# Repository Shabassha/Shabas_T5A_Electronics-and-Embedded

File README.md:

# 40V DC Motor H-Bridge Controller

## Overview
This repository contains the design files, simulations, and documentation for a 40V DC motor H-Bridge circuit capable of bidirectional control. The design was developed using a multi-stage validation approach: verifying the high-voltage logic and bootstrap physics in **Proteus**, followed by physical footprint mapping and PCB routing in **KiCad**.

## Key Features
* **High-Voltage Operation:** Designed to safely switch a 40V motor supply rail.
* **Hardware Shoot-Through Protection:** Utilizes dual IR2104 half-bridge gate drivers with built-in dead-time insertion, preventing cross-conduction.
* **Bootstrap Circuitry:** Integrated 10µF capacitors and fast-recovery diodes to safely drive the high-side N-Channel MOSFETs.
* **Optimized Power Routing:** High-current paths (40V IN, Motor Outputs) are routed with 1.5mm traces, while logic signals use standard 0.25mm traces.
* **Thermal Management:** Features a continuous bottom-layer copper ground pour to dissipate heat and shield logic inputs from high-voltage switching noise.

## Core Components
* **Gate Drivers:** 2x IR2104 (DIP-8)
* **Power MOSFETs:** 4x IRF540N (N-Channel, TO-220)
* **Terminals:** 5.08mm screw terminal blocks (Power & Motor), 2.54mm pin headers (Logic)
* **Passives:** 20Ω series gate resistors, 10µF radial electrolytic capacitors

## Repository Structure
* `/KiCad/` - Contains the schematic (`.kicad_sch`), PCB layout (`.kicad_pcb`), and 3D renders.
* `/Simulation/` - Contains the Proteus project files used to validate the gate driver logic.
* `/Docs/` - Contains the Bill of Materials (BOM) and the comprehensive Phase 2 Design Report (PDF).

## Getting Started
To view or modify the physical board layout:
1. Clone this repository.
2. Open the project file in [KiCad](https://www.kicad.org/).
3. To view the physical board, open the PCB Editor and press `Alt+3` to launch the 3D Viewer.

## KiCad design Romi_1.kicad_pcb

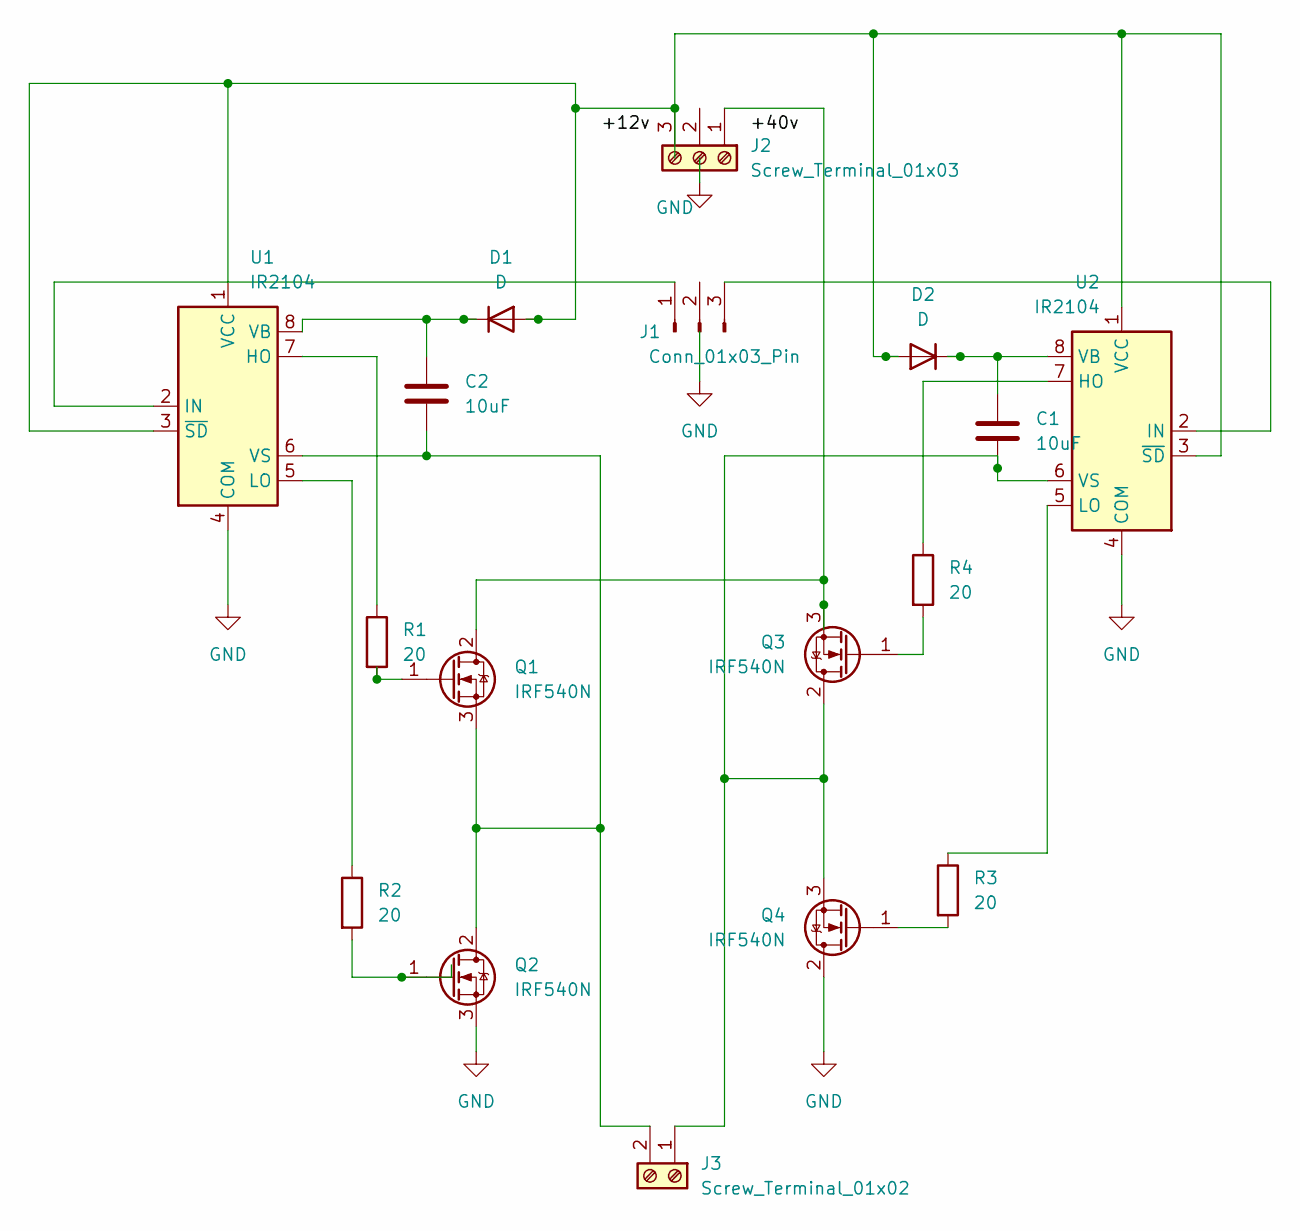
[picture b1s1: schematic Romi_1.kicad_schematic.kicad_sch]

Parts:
C1, C2: 10uF; CP_Radial_D5.0mm_P2.50mm
D1, D2: D; D_DO-41_SOD81_P10.16mm_Horizontal
J1: Conn_01x03_Pin; PinHeader_1x03_P2.54mm_Vertical
J2: Screw_Terminal_01x03; TerminalBlock_Phoenix_MKDS-1,5-3-5.08_1x03_P5.08mm_Horizont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
J3: Screw_Terminal_01x02; TerminalBlock_Phoenix_MKDS-1,5-2-5.08_1x02_P5.08mm_Horizont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
Q1, Q2, Q3, Q4: IRF540N; TO-220-3_Vertical
R1, R2, R3, R4: 20; R_Axial_DIN0207_L6.3mm_D2.5mm_P10.16mm_Horizontal
U1, U2: IR2104; DIP-8_W7.62mm

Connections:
GND: Q2.3 (S), Q4.2 (D), U1.4 (COM), U2.4 (COM)
unnamed: D1.2 (A), D2.2 (A), J2.3, U1.1 (VCC), U1.3 (~SD), U2.1 (VCC), U2.3 (~SD)
unnamed: C2.1, D1.1 (K), U1.8 (VB)
unnamed: C1.1, D2.1 (K), U2.8 (VB)
unnamed: J1.1, U1.2 (IN)
unnamed: J1.3, U2.2 (IN)
unnamed: J2.1, Q1.2 (D), Q3.3 (S)
unnamed: C1.2, J3.1, Q3.2 (D), Q4.3 (S), U2.6 (VS)
unnamed: C2.2, J3.2, Q1.3 (S), Q2.2 (D), U1.6 (VS)
unnamed: Q1.1 (G), R1.2
unnamed: Q2.1 (G), R2.2
unnamed: Q3.1 (G), R4.2
unnamed: Q4.1 (G), R3.2
unnamed: R1.1, U1.7 (HO)
unnamed: R2.1, U1.5 (LO)
unnamed: R4.1, U2.7 (HO)
unnamed: R3.1, U2.5 (LO)

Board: 2 copper layers, 17 parts (0 on the bottom side), 17 nets, no tracks yet.

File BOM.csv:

"Reference","Qty","Value","DNP","Exclude from BOM","Exclude from Board","Footprint","Datasheet"
"C1,C2","2","10uF","","","","Capacitor_THT:CP_Radial_D5.0mm_P2.50mm",""
"D1,D2","2","D","","","","Diode_THT:D_DO-41_SOD81_P10.16mm_Horizontal",""
"J1","1","Conn_01x03_Pin","","","","Connector_PinHeader_2.54mm:PinHeader_1x03_P2.54mm_Vertical",""
"J2","1","Screw_Terminal_01x03","","","","TerminalBlock_Phoenix:TerminalBlock_Phoenix_MKDS-1,5-3-5.08_1x03_P5.08mm_Horizontal",""
"J3","1","Screw_Terminal_01x02","","","","TerminalBlock_Phoenix:TerminalBlock_Phoenix_MKDS-1,5-2-5.08_1x02_P5.08mm_Horizontal",""
"Q1,Q2,Q3,Q4","4","IRF540N","","","","Package_TO_SOT_THT:TO-220-3_Vertical","http://www.irf.com/product-info/datasheets/data/irf540n.pdf"
"R1,R2,R3,R4","4","20","","","","Resistor_THT:R_Axial_DIN0207_L6.3mm_D2.5mm_P10.16mm_Horizontal",""
"U1,U2","2","IR2104","","","","Package_DIP:DIP-8_W7.62mm","https://www.infineon.com/dgdl/ir2104.pdf?fileId=5546d4625336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"
